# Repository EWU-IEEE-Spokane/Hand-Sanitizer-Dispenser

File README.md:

# Hand-Sanitizer-Dispenser

Project Documentation can be found at: 
https://hand-sanitizer-dispenser.readthedocs.io/en/latest/

Purpose:  During the pandemic touching a hand-sanitizer pump that many other people have touched is almost counter-intuitive for preventing the spread of disease. We aim to provide people with a touch-free hand-sanitizer dispenser with two pathways to execution. The first is to create a product as low-cost as possible that can be easily mass-produced and used as a fundraiser with the goal of fundraising at least $300. The other is to create a smart dispenser that can connect to a network and teach us more about the internet of things. 

Expected Outcomes:
      Dispense hand-sanitizer without touching
Create a product for under $10 to mass-produce and fundraise
Possible sensors to implement for cost savings: PIR (10/$15), distance(5 / $8.39), thermoresistor(30/$5), photoresistor(10/$10), infrared sensor(10/$10.31)
**check the ranges of each sensor/design awareness

A network of devices that communicates with each other 

Possible Features: solar charging, power management circuits, cybersecurity measures

Possible data to collect:  #  of uses, time to refill, time of day most used, if multiple stations then location used most, the temperature of the user, ambient temperature, solar irradiance

Technical Learning Goals:
Prepare cost estimations with cost-benefit analysis for various designs
Learn how to connect to a device to a network
Implement software for the device to interface with 
Develop awareness of potential cybersecurity flaws with the device and network

Collaborative Learning Goals:
Marketing and advertising product in virtual environment
Network with supporters and donors

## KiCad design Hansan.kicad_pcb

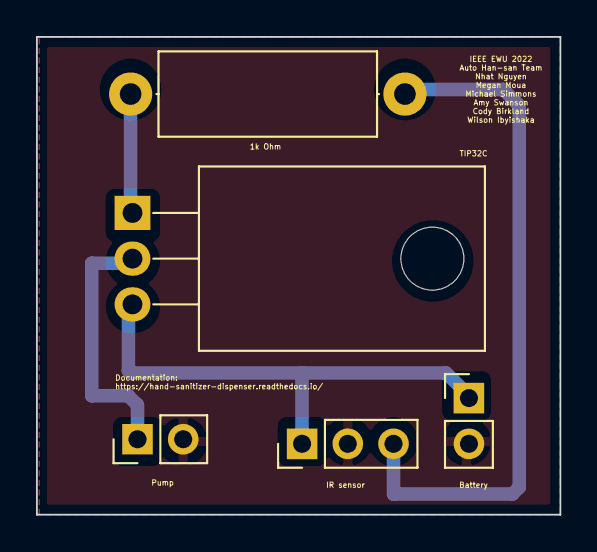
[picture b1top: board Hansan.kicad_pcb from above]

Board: 2 copper layers, 29.1 x 26.5 mm, 5 parts (0 on the bottom side), 5 nets.

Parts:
1k Ohm : 1kOhm; R_Axial_DIN0414_L11.9mm_D4.5mm_P15.24mm_Horizontal
Battery: Battery; PinHeader_1x02_P2.54mm_Vertical
IR sensor: IR Sensor; PinHeader_1x03_P2.54mm_Vertical
Pump: Pump; PinHeader_1x02_P2.54mm_Vertical
TIP32C: TIP32C; TO-220-3_Horizontal_TabDown

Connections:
GND: Battery.2, IR sensor.2, Pump.2
unnamed: Battery.1, IR sensor.1, TIP32C.3
unnamed: 1k Ohm.2, IR sensor.3
unnamed: Pump.1, TIP32C.2
unnamed: 1k Ohm.1, TIP32C.1

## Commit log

2020-12-15 Added readthedocs
2020-12-15 Updated docs
2020-12-17 guinea pigs are cute
2020-12-17 Bunnies are cute
2021-01-08 minutes
2021-01-18 updated getting started page
2021-02-12 updates
    product dimensions, meetings on Friday at 1pm
